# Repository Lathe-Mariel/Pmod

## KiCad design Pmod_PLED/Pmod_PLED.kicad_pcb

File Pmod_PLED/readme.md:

# Pmod Power_ColorLED
　Pmod規格に準拠したマイコン/FPGAボード用拡張基板です．  
 KiCADのプロジェクトになっています．  
 ガーバーの最終出力は面付け（4つ取り）してあり，kikitディレクトリに入っています．  
 アルミの片面基板を想定しており，JLCPCBで制作後，動作確認してあります．

# BOM
一部は汎用部品ですが無理やり表面実装します．  

## TBD62064APG
東芝のトランジスタアレイです．電流に余裕のあるDIPを選定．

## SS2040FL ショットキダイオード
RGBのうち，RだけVfが低いのでバランス取りとして入れています．  
RGB間の出力もPWMで調整する場合は，ソルダージャンパ直結でヨシッ！

## 外部電源
電源はPmod（Vcc）とDCジャック（ExVcc）から選択できます．  
どちらを使うかはピンヘッダ（3pin）で選択できるようにしてあります．  
片方のみを使用する場合は，ピンヘッダを実装せずに基板上で直結（3pinの'Vcc'と'中央のピン'）してもよいでしょう．

### AZ1117-3.3
DCレギュレータです．
電源としてPmodのVccのみを使う場合は，実装する必要はありません．  
その場合，基板を折ることで基板長を短くできるようになっています．ﾎﾟｷｯっとな  

# はんだ付け
アルミ基板なので，まぁ付かないです．  
筆者はホットプレート（100℃設定）に基板を置いた状態ではんだこてで手付けしています．  
はんだこてだけでは，かなり厳しいでしょう．  

# サンプルプログラム
Tang Primer 20Kに接続して使うサンプルプログラムです．  
Gowin EDAのプロジェクトになっています．

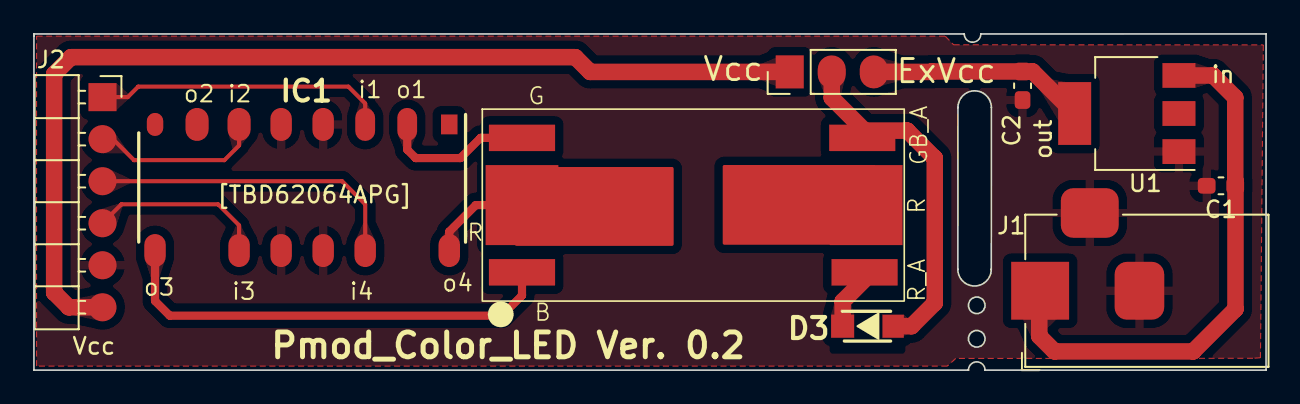
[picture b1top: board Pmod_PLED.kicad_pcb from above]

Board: 2 copper layers, 74.5 x 20.3 mm, 9 parts (0 on the bottom side), 5 nets.

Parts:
C1, C2: 0.1u; C_0603_1608Metric_Pad1.08x0.95mm_HandSolder
D1: EP204K-150G1R1B1-CA; EP204-150G1R1B1-CA
D3: SS2040FL; SODFL3618X108N
IC1: TBD62064APG; DIP762W60P254L1975H445Q16N
J1: Barrel_Jack_Switch; BarrelJack_Horizontal
J2: Conn_01x06_Pin; Pmod6
J3: Conn_01x03_Pin; PinHeader_1x03_P2.54mm_Vertical
U1: AMS1117-3.3; SOT-223-3_TabPin2

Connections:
/Anode: D1.6 (A), D3.2 (A)
/ExVcc: C2.2, U1.2 (VO)
GND: C1.2, C2.1, U1.1 (GND)
unnamed: D1.4 (RA), D3.1 (K)
unnamed: C1.1, U1.3 (VI)

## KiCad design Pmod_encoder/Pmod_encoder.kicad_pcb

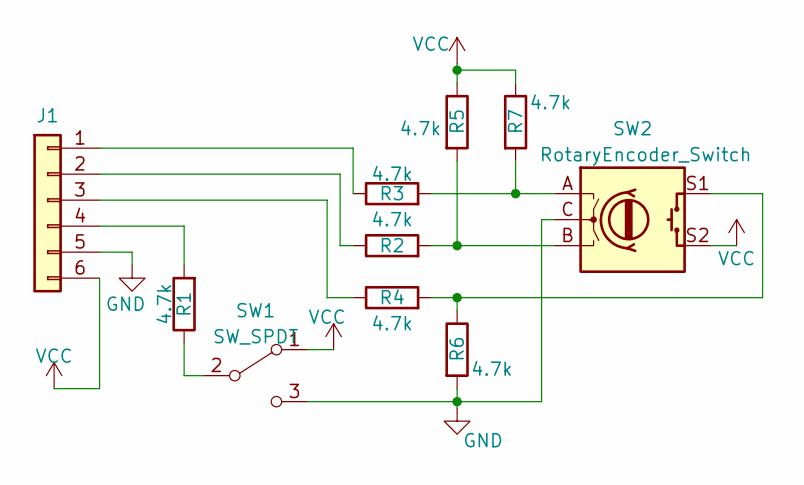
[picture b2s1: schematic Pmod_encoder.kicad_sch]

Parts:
J1: Pmod6
R1, R2, R3, R4, R5, R6, R7: 4.7k; Resistor_SMD_THT
SW1: SW_SPDT; PinHeader_1x05_P2.54mm_Vertical
SW2: RotaryEncoder_Switch; RotaryEncoder_Alps_EC11E-Switch_Vertical_H20mm

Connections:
GND: J1.5, R6.2, SW1.3 (C), SW2.C
unnamed: J1.1, R3.1
unnamed: J1.2, R2.1
unnamed: J1.3, R4.1
unnamed: J1.4, R1.2
unnamed: R2.2, R5.2, SW2.B
unnamed: R3.2, R7.2, SW2.A
unnamed: R4.2, R6.1, SW2.S1
unnamed: R1.1, SW1.2 (B)
VCC: J1.6, R5.1, R7.1, SW1.1 (A), SW2.S2

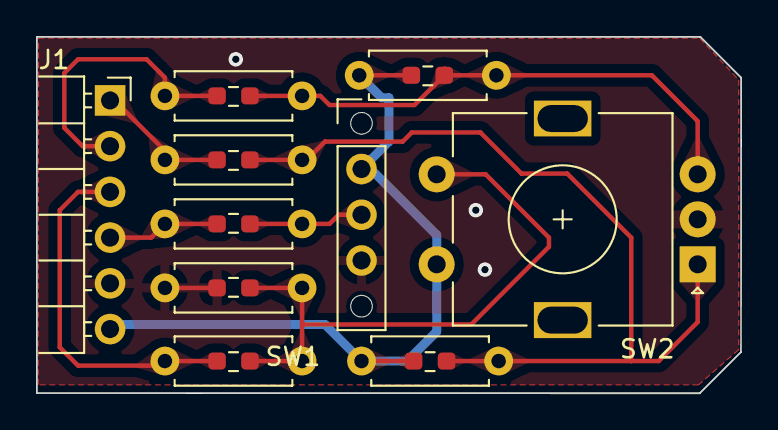
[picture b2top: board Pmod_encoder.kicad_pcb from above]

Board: 2 copper layers, 39.1 x 19.8 mm, 10 parts (0 on the bottom side), 10 nets.
